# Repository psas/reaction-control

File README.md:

reaction-control
================

## Overview
We want active stabilization for LV3, but wish to escape the vexxing dynamic pressure limitations of the present aerodyamic canard based [roll-control system](https://github.com/psas/roll-control) used on LV2.3.

The concept:
* Cold-gas rocket propulsion
* 8 N thrust (roll), 11 N (pitch x, y)
* Nitrogen tank at 4500 psi
* 8x 3D-printed bell nozzles
* PWM throttling
* "Robust control"

Rao bells (e.g. nearly ideal nozzles) are hard to machine c.f. conical nozzles, but easy to 3D print. This also enables “plug & play” optimal expansion ratios for any trajectory. Here is the basic workflow:
* Determine flight envelope from simulation (for instance, using [OpenRocket](https://github.com/psas/lv3.0-airframe/tree/master/sim/ORK))
* Run `nozzle_sizing.m` script to determine nozzle design parameters
* Plug expansion ratio into parametric solid model and export `.stl`
* Print nozzles, install in carrier ring
* ???
* Fly!

This repo includes mathematical models, matlab and python controller scripts, eagle files for a custom MOSFET relay board, solenoid PWD test data for transfer functions, system test data and bode analysis, and the Solidworks CAD assembly for the LV3 Reaction Control System.

## Suplimentary Links
[Link to AIAA SPACE 2015 presentation slides](https://docs.google.com/presentation/d/1vfhgjRymidfKbpzjqC0tfAL57iSsNFOEQSFTw5_EEGs/edit?usp=sharing)

[Link to AIAA SPACE 2015 conference proceedings paper](https://github.com/psas/reaction-control/blob/master/pubs/AIAA%20RCS%20Manuscript_FINAL2.pdf)

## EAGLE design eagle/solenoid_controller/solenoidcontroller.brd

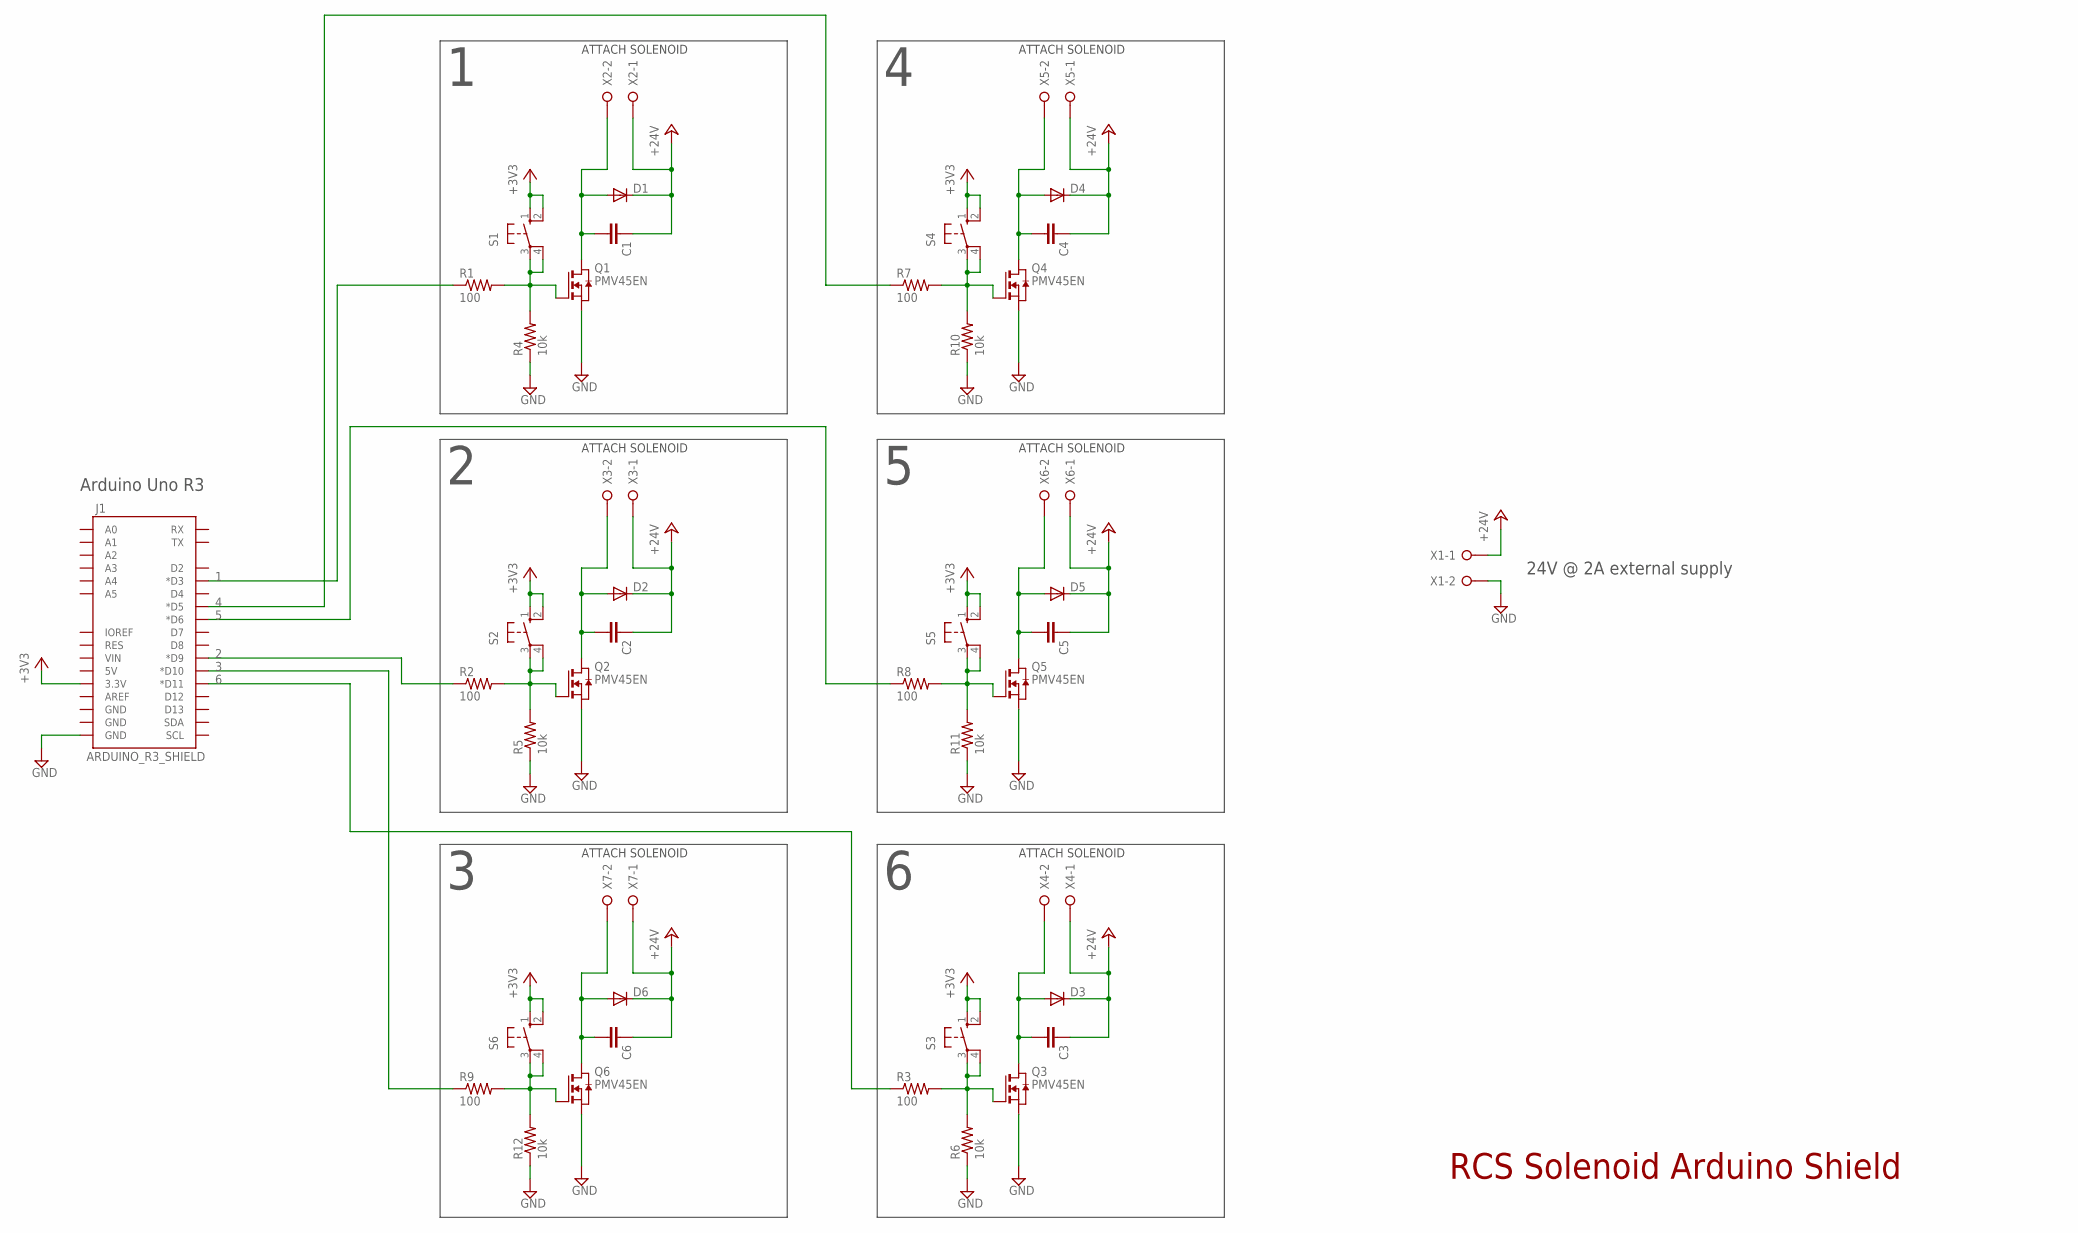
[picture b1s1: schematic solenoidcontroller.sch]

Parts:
C1, C2, C3, C4, C5, C6: C-EUC0603; C0603
D1, D2, D3, D4, D5, D6: DIODE-DO214BA; DO214BA
J1: ARDUINO_R3_SHIELD; UNO_R3_SHIELD
Q1, Q2, Q3, Q4, Q5, Q6: PMV45EN; SOT23
R1, R2, R3, R7, R8, R9: 100; R0603
R4, R5, R6, R10, R11, R12: 10k; R0603
S1, S2, S3, S4, S5, S6: 10-XX; B3F-10XX
X1, X2, X3, X4, X5, X6, X7: W237-02P; W237-132

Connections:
1: J1.D3 (*D3), R1.1
2: J1.D9 (*D9), R2.1
3: J1.D10 (*D10), R9.1
4: J1.D5 (*D5), R7.1
5: J1.D6 (*D6), R8.1
6: J1.D11 (*D11), R3.1
+3V3: J1.3.3V, S1.1 (S), S1.2 (S1), S2.1 (S), S2.2 (S1), S3.1 (S), S3.2 (S1), S4.1 (S), S4.2 (S1), S5.1 (S), S5.2 (S1), S6.1 (S), S6.2 (S1)
+24V: C1.1, C2.1, C3.1, C4.1, C5.1, C6.1, D1.C, D2.C, D3.C, D4.C, D5.C, D6.C, X1.1, X2.1, X3.1, X4.1, X5.1, X6.1, X7.1
GND: J1.GND@0 (GND), Q1.2 (S), Q2.2 (S), Q3.2 (S), Q4.2 (S), Q5.2 (S), Q6.2 (S), R4.1, R5.1, R6.1, R10.1, R11.1, R12.1, X1.2
unnamed: Q2.1 (G), R2.2, R5.2, S2.3, S2.4 (P1)
unnamed: Q3.1 (G), R3.2, R6.2, S3.3, S3.4 (P1)
unnamed: C2.2, D2.A, Q2.3 (D), X3.2
unnamed: C3.2, D3.A, Q3.3 (D), X4.2
unnamed: Q1.1 (G), R1.2, R4.2, S1.3, S1.4 (P1)
unnamed: C1.2, D1.A, Q1.3 (D), X2.2
unnamed: Q4.1 (G), R7.2, R10.2, S4.3, S4.4 (P1)
unnamed: C4.2, D4.A, Q4.3 (D), X5.2
unnamed: Q5.1 (G), R8.2, R11.2, S5.3, S5.4 (P1)
unnamed: C5.2, D5.A, Q5.3 (D), X6.2
unnamed: Q6.1 (G), R9.2, R12.2, S6.3, S6.4 (P1)
unnamed: C6.2, D6.A, Q6.3 (D), X7.2

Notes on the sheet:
ATTACH SOLENOID
24V @ 2A external supply
Arduino Uno R3
RCS Solenoid Arduino Shield

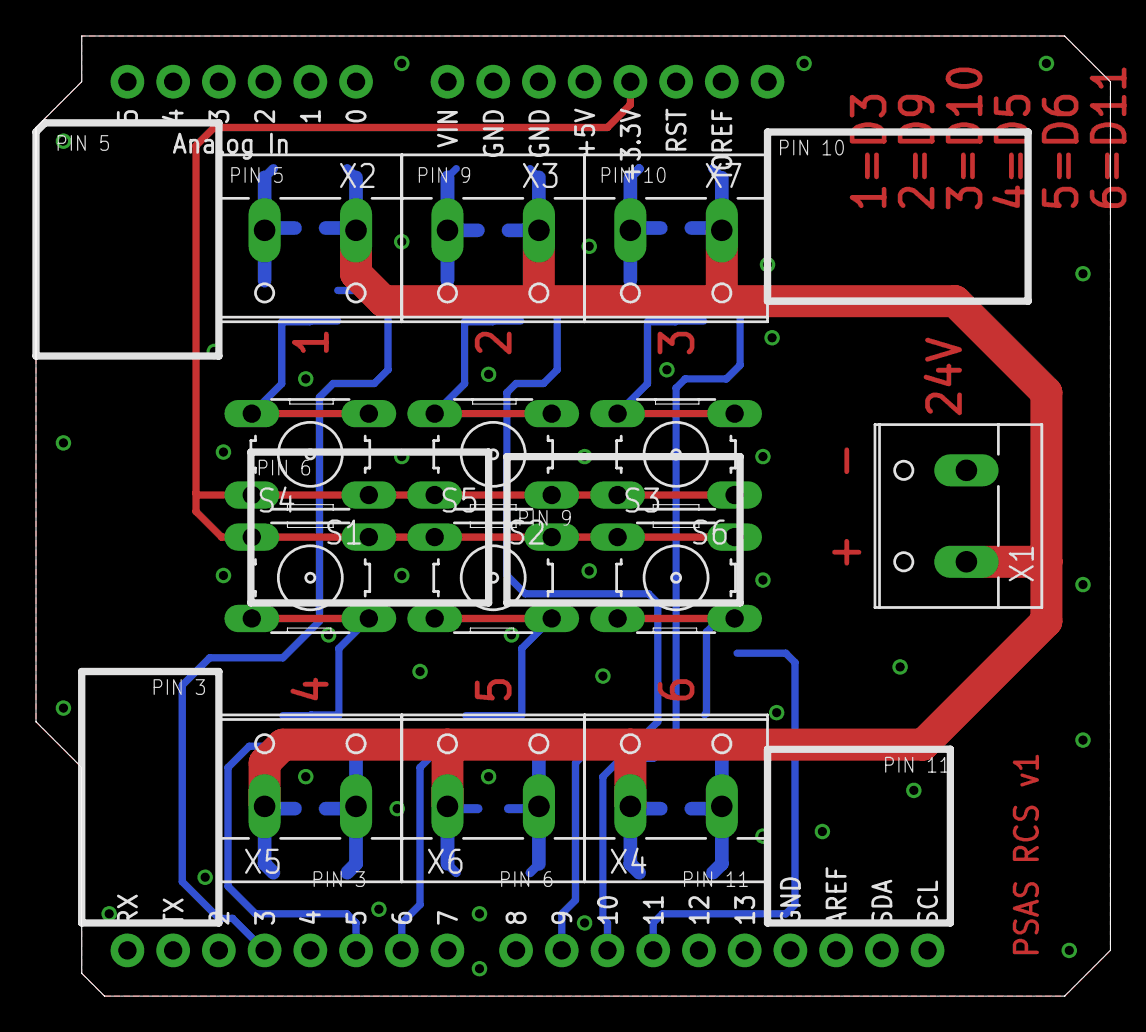
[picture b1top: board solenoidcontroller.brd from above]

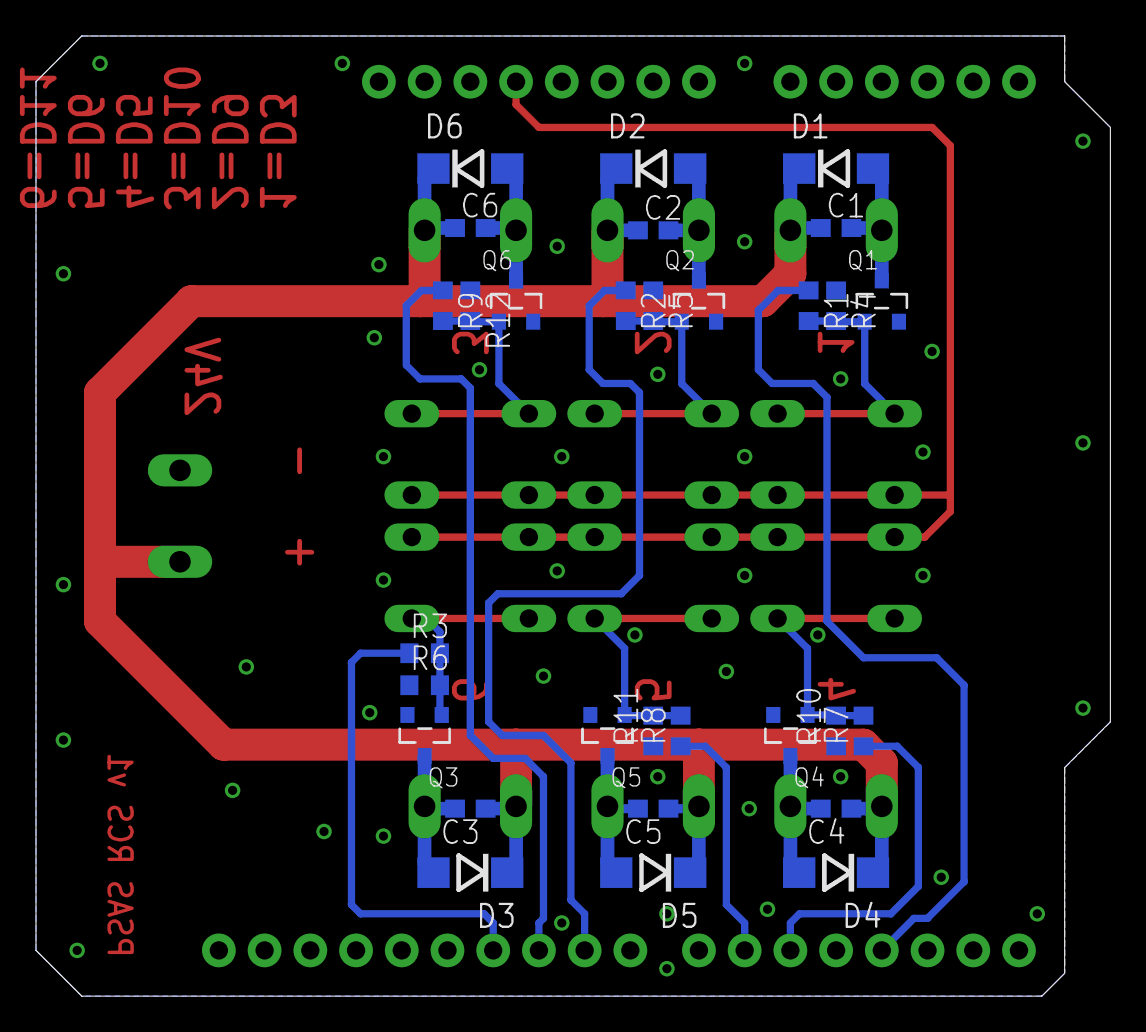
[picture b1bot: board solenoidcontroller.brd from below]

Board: 2 copper layers, 59.7 x 53.3 mm, 44 parts (30 on the bottom side), 21 nets.

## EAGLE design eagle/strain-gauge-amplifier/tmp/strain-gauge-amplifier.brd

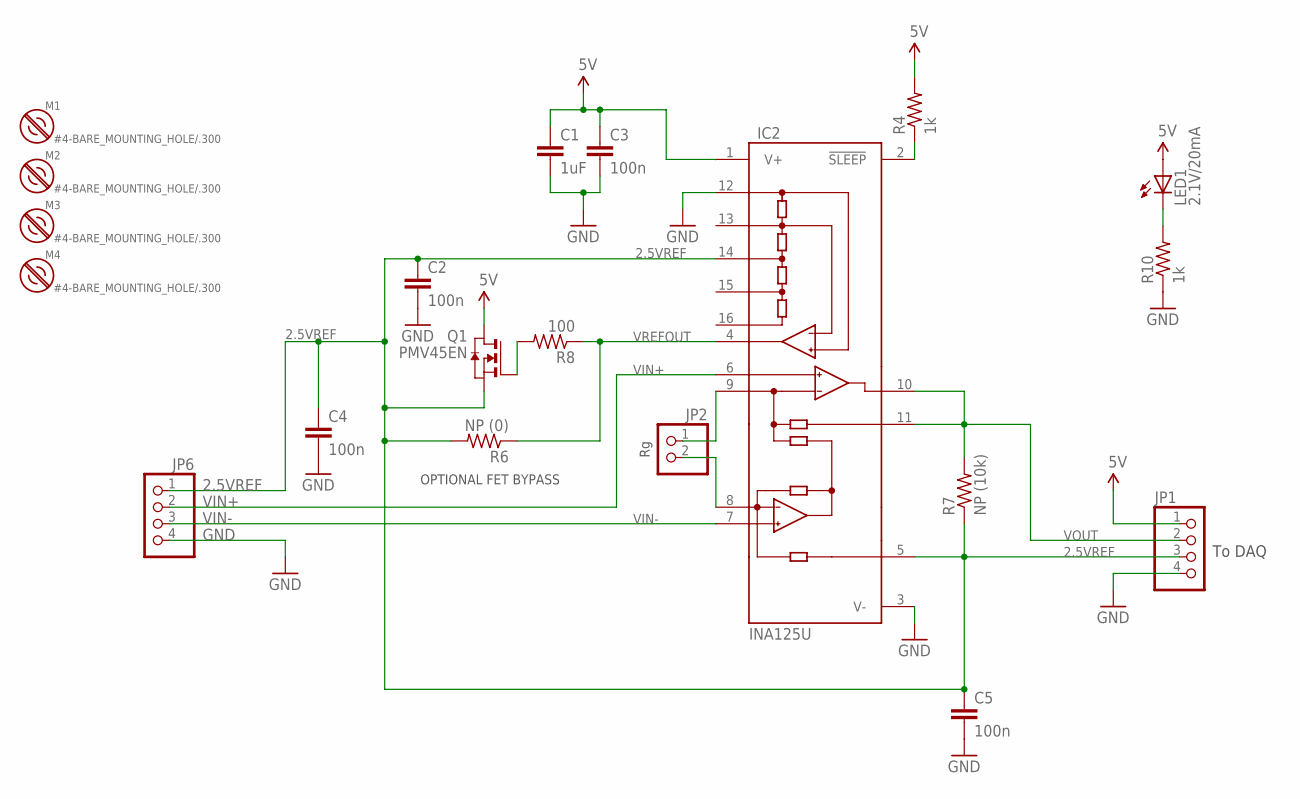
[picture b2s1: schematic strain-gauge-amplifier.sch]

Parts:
C1: 1uF; 0805-C-NOSILK
C2, C3, C4, C5: 100n; 0805-C-NOSILK
IC2: INA125U; SO16-1
JP1, JP6: PINHD-1X4; 1X04
JP2: PINHD-1X2; 1X02
LED1: 2.1V/20mA; LED-0603
M1, M2, M3, M4: #4-BARE_MOUNTING_HOLE/.300; #4/.300-BARE+STD_NUT_OR_STAR_WASHER
Q1: PMV45EN; SOT23
R4, R10: 1k; 0805-C-NOSILK
R6: NP (0); 0805-C-NOSILK
R7: NP (10k); 0805-C-NOSILK
R8: 100; 0805-C-NOSILK

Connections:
2.5VREF: C2.1, C4.1, C5.1, IC2.5 (REF), IC2.14 (REF2.5), JP1.3, JP6.1, Q1.2 (S), R6.2, R7.1
5V: C1.1, C3.1, IC2.1 (V+), JP1.1, LED1.A, Q1.3 (D), R4.2
GND: C1.2, C2.2, C3.2, C4.2, C5.2, IC2.3 (V-), IC2.12 (REFCOM), JP1.4, JP6.4, R10.1
unnamed: IC2.9 (RG), JP2.1
unnamed: IC2.8 (RG), JP2.2
unnamed: Q1.1 (G), R8.2
unnamed: IC2.2 (!SLEEP), R4.1
unnamed: LED1.C, R10.2
VIN+: IC2.6 (+IN), JP6.2
VIN-: IC2.7 (-VIN), JP6.3
VOUT: IC2.10 (OUT), IC2.11 (SENSE), JP1.2, R7.2
VREFOUT: IC2.4 (REFOUT), R6.1, R8.1

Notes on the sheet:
OPTIONAL FET BYPASS
To DAQ

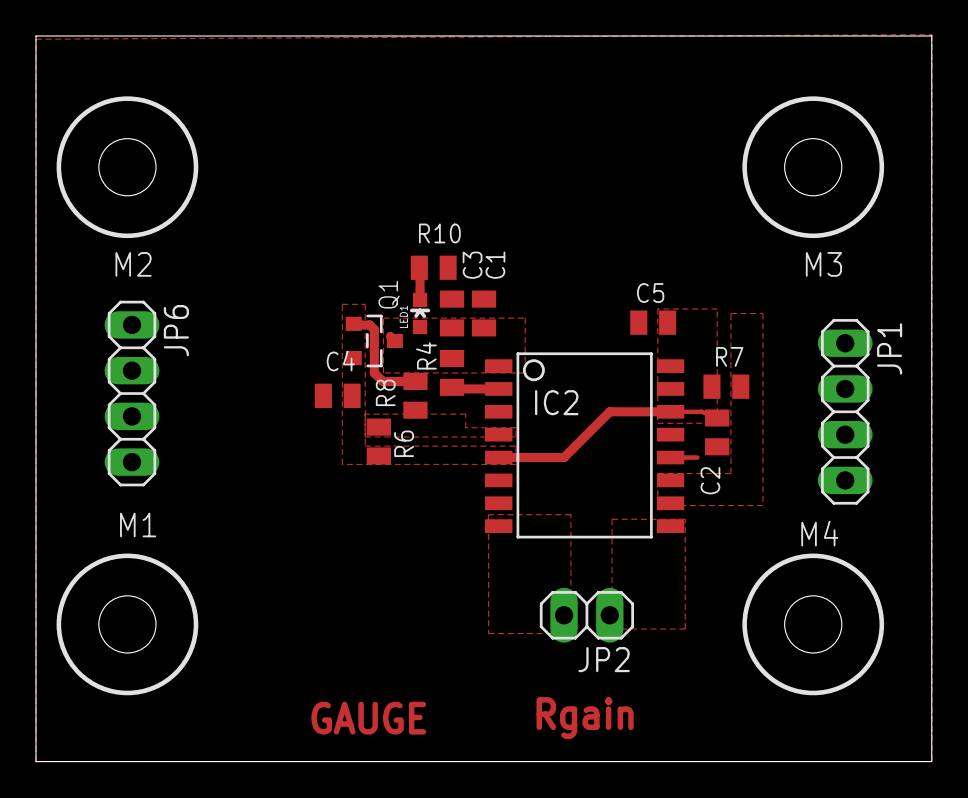
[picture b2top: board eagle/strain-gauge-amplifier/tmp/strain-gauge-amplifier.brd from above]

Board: 2 copper layers, 49.8 x 40.3 mm, 20 parts (0 on the bottom side), 12 nets.

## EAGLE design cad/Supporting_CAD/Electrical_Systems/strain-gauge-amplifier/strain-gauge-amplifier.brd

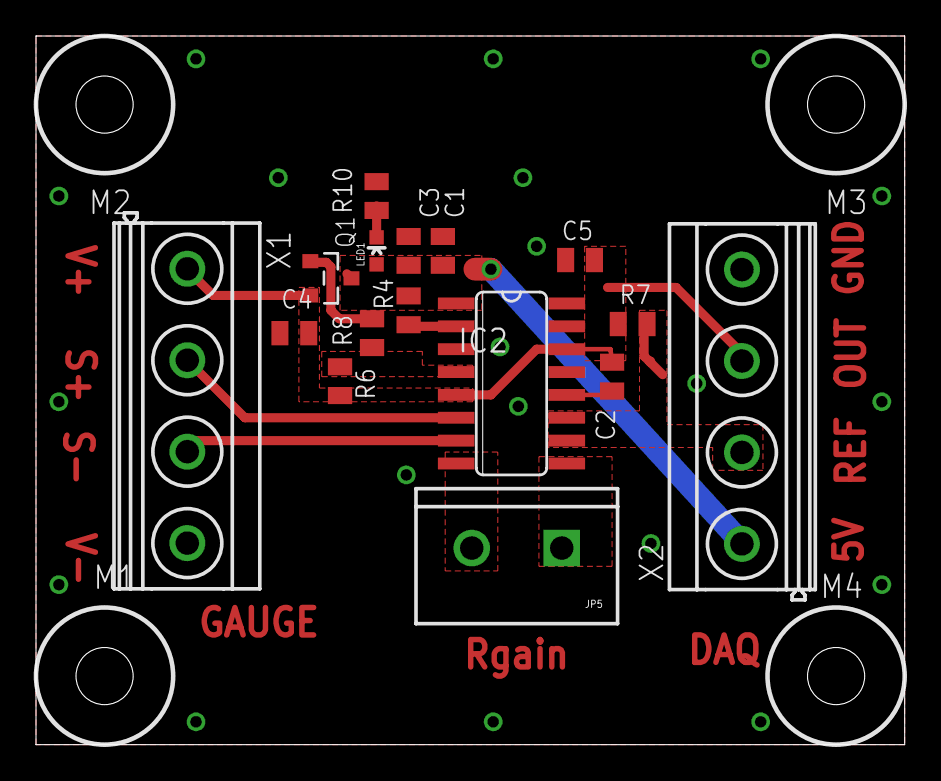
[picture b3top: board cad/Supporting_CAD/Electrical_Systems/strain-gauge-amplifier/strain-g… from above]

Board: 2 copper layers, 48.3 x 39.4 mm, 20 parts (0 on the bottom side), 12 nets.

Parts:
C1: 1uF; 0805-C-NOSILK
C2, C3, C4, C5: 100n; 0805-C-NOSILK
IC2: INA125; SO16
JP5: Rg; SCREWTERMINAL-5MM-2
LED1: 2.1V/20mA; LED-0603
M1, M2, M3, M4: #4-BARE_MOUNTING_HOLE/.300; #4/.300-BARE+STD_NUT_OR_STAR_WASHER
Q1: PMV45EN; SOT23
R4, R10: 1k; 0805-C-NOSILK
R6: NP (0); 0805-C-NOSILK
R7: NP (10k); 0805-C-NOSILK
R8: 100; 0805-C-NOSILK
X1, X2: MKDSN1,5/4-5,08

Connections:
2.5VREF: C2.1, C4.1, C5.1, IC2.5, IC2.14, Q1.2, R6.2, R7.1, X1.1, X2.3
5V: C1.1, C3.1, IC2.1, LED1.A, Q1.3, R4.2, X2.1
GND: C1.2, C2.2, C3.2, C4.2, C5.2, IC2.3, IC2.12, R10.1, X1.4, X2.4
unnamed: IC2.7, X1.3
unnamed: IC2.9, JP5.1
unnamed: IC2.8, JP5.2
unnamed: Q1.1, R8.2
unnamed: IC2.2, R4.1
unnamed: LED1.C, R10.2
VIN+: IC2.6, X1.2
VOUT: IC2.10, IC2.11, R7.2, X2.2
VREFOUT: IC2.4, R6.1, R8.1

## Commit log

2014-10-10 Sea Level test nozzle CAD and drawings
2014-10-10 Reorganize
2014-10-10 Matlab models
2014-10-10 more stuff and things
2014-10-25 first attempt at a complete module for the RCS
2014-12-17 delaval nozzles
2014-12-17 half cone
2014-12-17 nevermind
    I don't want those crappy .sdlprt files any ways
2015-01-15 ignore solidworks recovery files
2015-01-15 updated adapter
2015-01-20 solidworks nozzles
2015-01-20 Revert "nevermind"
    This reverts commit 430d1ab73a2580e48ba750538cf57433fbc770e6.
    Conflicts:
    3d Printing nozzles/deLaval.SLDPRT
2015-01-20 one more time
2015-02-14 Roll Control Files
    Beginning work on modeling roll dynamics of LV 3 rocket and controller
2015-03-02 Update RCS_thermoDYNAMICS.m
    Automatically calculated initial conditions, corrected mass flow rate relation, corrected solenoid Cv relation.
2015-03-02 Update RCS_thermoDYNAMICS.m
    Spelling, removed useless comments
2015-03-02 Update RCS_thermoDYNAMICS.m
    While loop conditions
2015-03-04 updates and old versions of nozzle ring
    has new designs of the nozzles (pitch and roll are combined to one
    printed part)
2015-03-05 working on combined nozzles with scarfing calculations
2015-03-05 added equations that give the effective expansion ratio of the scarfed nozzles
2015-03-06 updating models
2015-03-07 started drawing for nozzle ring
2015-03-10 added first test of single stream
2015-03-10 removed datasheet
2015-03-10 Revert "removed datasheet"
    This reverts commit 2f5248cdd5a37d6b0d12954012879737604eaedc.
2015-03-10 deleteing unneccessary bs
2015-03-11 added new test data
2015-03-11 simple force graphs
2015-03-12 Added lumped-capacitance estimation of solenoid seal chilling
2015-03-12 added second test session data
2015-03-13 added calibrated data to the excel files
2015-03-13 formatting changes
2015-03-13 fixed calibrations
2015-03-13 checking interference in the pressure sensor data
2015-03-15 added filtered data
2015-03-15 adding model pictures and filter script
2015-03-15 added graphs for data
2015-03-16 now uses double-precision floating point math, prints data to a space delimited .txt
2015-03-16 stuff
2015-03-20 stuff (nozzle ring stl)
2015-03-21 single stream data for paper
2015-03-22 working on fitting everything into the module (stuff)
    added swagelock regulator, solenoids, tube fittings, etc
2015-03-23 I don't remember what I was doing... oh well
2015-03-23 pitch nozzle stl
2015-03-23 adding tubing to the drawings
    fyi the solidworks tube routing add-on is a piece of garbage
2015-03-24 stuffy stuff from meeting
2015-03-30 controller for arduino
2015-03-30 sdflk
2015-03-30 asdlv
2015-03-30 Duty Cycle controller
    Allows for variation in duty cycle with no delay
2015-03-30 Update RCS_Arduino_controller__BANG__.ino
    added negatives for roll rate
2015-03-30 Update RCS_Arduino_controller__BANG__.ino
    fixed the negatives issue
2015-03-30 made rate control into a class
2015-03-30 Update RCS_Arduino_controller__BANG__.ino
    changed it back.... thanks brent...... :p
2015-03-30 fixed rates for correct coordinates
2015-03-30 moved duty cycle to a new folder
2015-03-30 changed pin declarations
    and added pitch, yaw assignments and added pinModes
2015-03-30 added pitch and yaw rate bang bang
2015-03-30 pitch and yaw controllers
    bang bang based on accelerometer
2015-04-01 removed outdated solidworks files
    and rearranged some stuff
2015-04-01 stuff and things (nothing was actually changed)
2015-04-02 modified the solenoids
    added a chamfer that is .3 in x .152 in
2015-04-02 added deLaval geometry to all nozzles
2015-04-02 added new STL of the ring and more expansion ratios
2015-04-03 adding part files for all of the expansion ratios
2015-04-03 Duty cycle without Delay
2015-04-03 imported simple feedback loop
2015-04-03 moving to arduino data collection
    fuck labview... fuck labjack
2015-04-04 data collection
2015-04-05 Added solenoid controller schematic and board
2015-04-05 Cleaned up Baker's already A-OK board. Switched kickback components to bottom to minimimze copper length, fattened up power traces and reduced length, added text on top layer, re-numbered the solenoi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
2015-04-05 Updated solenoid controller board; moved all SMD components to bottom layer and power traces to top layer.
2015-04-05 Generated new gerbers from Baker's commit.
2015-04-06 Data collection from arduino to csv
2015-04-08 adding tank braces
2015-04-08 bracing
2015-04-09 started regulator bracing
2015-04-10 added solenoid bracing and fixed dependencies
2015-04-14 working on the solenoid bracket
2015-04-15 started making ridgidity changes to solendoids
    started making manifold
2015-04-15 added laser cutting drawings and FEA
2015-04-16 Old strain gauge amplifer from airframe project. Comitting just for safety.
2015-04-17 new straingauge board for 4 white strain gauge.
2015-04-17 added a shower head
2015-04-17 Components with Electrical needs
    List of components with electrical needs in the RCS
2015-04-23 added manifold ideas
2015-04-23 added one piece manifold to assembly
2015-04-24 Nice readme for solinoid board
2015-04-25 RCS with feed back and gain
    takes IMU data and converts error to duty cycle output, which can be
    directly proportional to thrust.
2015-04-28 single stream testing
2015-04-28 Turns nozzle on for short duration after delay
2015-04-28 force calibration
2015-04-29 100 ms single stream test data
2015-05-02 single stream 5-2-15
2015-05-11 new regulator layout
2015-05-11 stuff from single stream testing
    not really sure what these files are but whatever, here they are
2015-05-12 nozzle cutaway
2015-05-13 inverted pendulum stand
2015-05-15 changed tube routing
2015-05-15 new nozzles for design test
2015-05-15 Newest roll_file
2015-05-15 roll_control file updated 5/152015
2015-05-16 changed variable types
2015-05-16 commented out the pressure sweep loop
2015-05-16 changed some parameters, commented out plots
2015-05-19 new nozzle designs and pressure calibration
2015-05-20 update of document to txt file
2015-05-20 added some research for the new IMU
    and pin designations for edison mini break out
2015-05-25 ported Gain_v2 to python2.7 now called Gain_v3
    and added inso for the new IMU
2015-05-29 optimized parameters: gains, roll rate limits, averaging amounts
2015-05-29 Finalized Roll-Control for first order
2015-05-29 more stuff YAY
2015-05-31 RCS Inverted Pendulum
2015-05-31 PWM Inverted Pendulum script
    updating changes
2015-05-31 Update Working code
    Timers are working correctly for PWM for Pitch only. Next step is
    implement a controller and then look at adding Yaw.
2015-05-31 impulse to controller
2015-06-02 Wider isolation on the solenoid controller board
2015-06-03 1 axis Inverted Pendulum Code v1.5
2015-06-11 adjusting parts
2015-06-11 adjusted manifold to reflect reality
2015-06-17 new single stream size testing
2015-07-29 Plotted data from most recent single-stream test
2016-03-08 Reorganization of repo
2016-03-09 adding datasheets
2017-03-09 reorganization, and added a bunch of old files
2017-03-09 made the readme less awful
2017-03-09 fixed list
2017-08-01 updated to latest version of SW
    This is the long commit message.
    Lorem ipsum dolor sit amet...
    The quick brown fox jumps over the lazy dog.
2018-05-07 Created blank nozzle insert for 3-port
2018-05-07 Created blank nozzle insert for single port
2020-11-18 first draft of a manual venting procedure
2020-11-19 draft of filling procedure
    big TODOs:
    - procedure for transporting tank
    - procedure for cleaning fittings
    - identifying necessary PPE
2021-04-04 first draft of the flight fittings diagram
    There's a lot of missing info and conflicts.
    - The regulator is nickel-plated aluminum (6061). I think there's another plated component somewhere. Someone should look into the reliability of nickel plating in preventing corrosion.
    - The LPFlight relief valve (PRV-01) seems to be spec'd oddly. It uses a brass body instead of stainless and a Viton seal instead of Buna-N.
    - PRV-01 also uses a burst-disk symbol instead of a relief valve symbol. Since there seem to be different standards for this, I would like us to compile a short list of "RCS-canonical" symbols.
    - The HPFlight tank should have a more unique desgnator than just "N2". I propose "HPFT".
2021-04-07 started diagrams for the fill and vent systems.
    Notes on fill system fittings diagram
    - What is the alloy of steel in the tank? "Steel" is not specific enough.
    (Strictly speaking, we mainly want to know the material of the outlet fitting on the valve.)
    This isn't a huge concern for corrosion, since this will only be installed for days (maybe weeks) at a time.
    - We should probably swap around the "fill hose coupling" and the "tower hose inlet coupling"
    to make the tower hose symmetrical.
2021-04-08 tiny tweaks (see long desc.)
    - The colors should now be legible on white or dark grey backgrounds.
    - The PRVs have actual PRV symbols instead of burst disk symbols.
    - The document now says what it's the source of truth (SoT) for, and
    calls out its upstream document.
    - The flexible hose for the launch tower is now symmetrical (female on
    both ends), so that it can't be attached backwards.
2021-06-19 random changes I forgot to commit
2021-06-19 assigned designators; minor fixes
2021-06-19 assigned designators to all the things!!!
2021-07-02 minor corrections from weekly meeting
2021-08-05 reconfigured LPL to use two on-off valves
    These are the same valves that the capstone used.
    I'm going to change some upstream stuff for the valves on the next
    commit.
2021-08-05 fixed typo
    was: male-male coupling said "female" on the ports
    is: says "male"
2021-08-05 refactored to use cross fitting in LPL
    This involved a surprising amount of rearranging.
2021-08-05 updated BoM link
    next steps:
    - assign designators to the new parts
    - update those designators in the BoM
    - add the capstone valves to the BoM
    - copy the info for the new parts into the diagram
    Ya know, if we just kept the BoM in the repo, we wouldn't need to worry
2021-08-11 updated part designators
    next tasks:
    - get part numbers and specs for solenoid valves and hardline tubing
2022-01-07 Added new controler script to improve upon
2022-01-16 resize page for easier viewing
2022-01-16 touched text to fix another display issue

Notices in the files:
parts and their libraries:
SparkFun-Connectors: Licensing: CC v3.0 Share-Alike You are welcome to use this library for commercial purposes.
SparkFun-Boards: Licensing: Creative Commons ShareAlike 4.0 International - https://creativecommons.org/licenses/by-sa/4.0
